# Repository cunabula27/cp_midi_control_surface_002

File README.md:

# midi_control_surface_002 Prototype
Midi Control Surface for Arduino Mega 2560 Rev3 running custom OpenDeck firmware available from www.shanteacontrols.com

This is the version that went into production and that I'm using myself. It contains some errors but they have no effect on functionality:

All the rotary potentiometers are wired in reverse, this is easily fixed by setting _Invert_ in the OpenDeck Configurator.

Also the rotary potentiometer footprints have incorrect design on the silk layer - I changed the type of potentiometer I was using after the boards were printed. Their physical footprint in the same but the sweep angle is greater so the panel graphics don't line up. This is purely cosmetic, but if you know me immensely annoying :)

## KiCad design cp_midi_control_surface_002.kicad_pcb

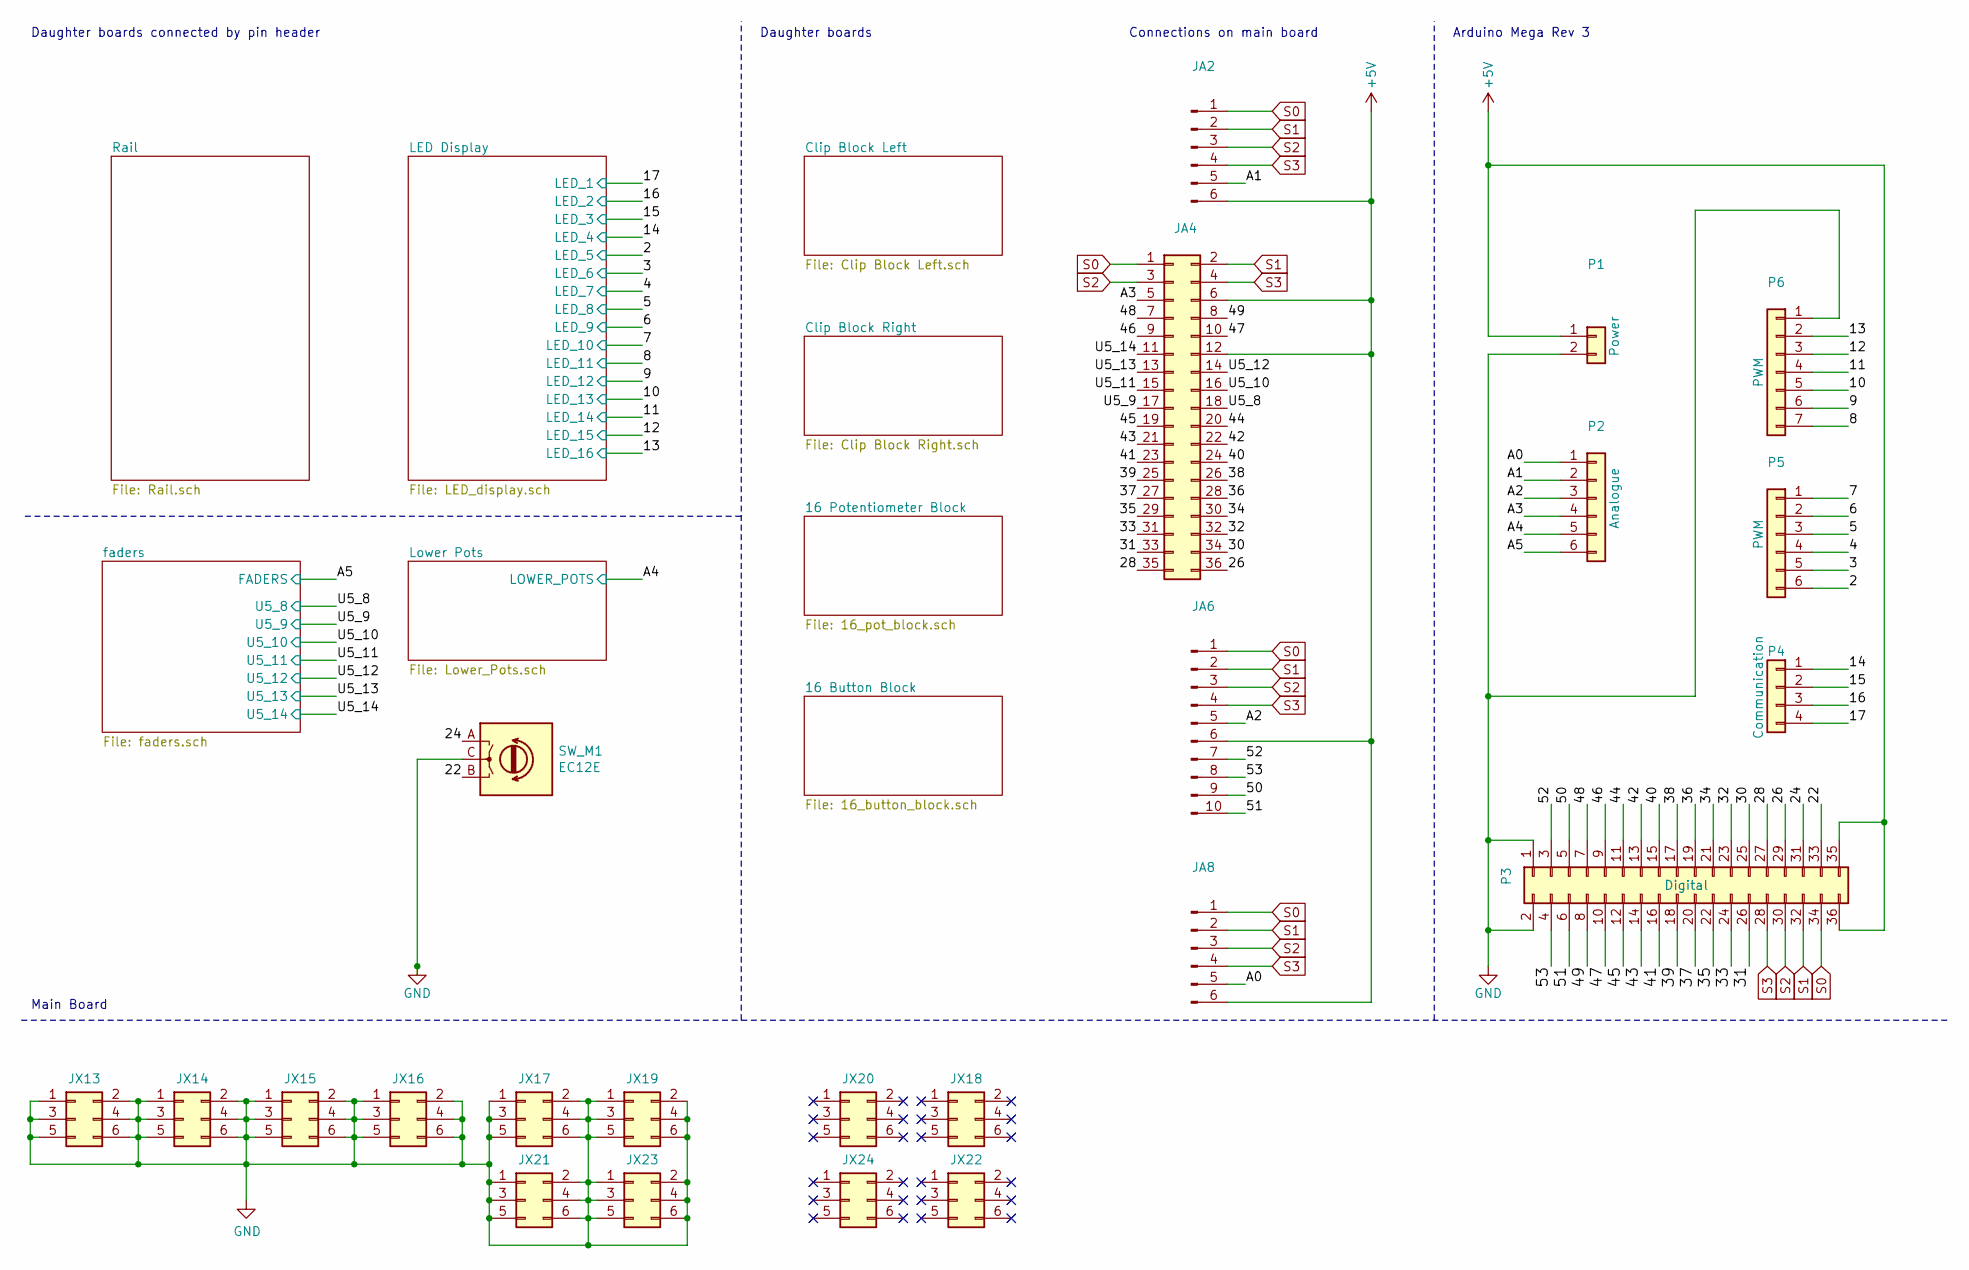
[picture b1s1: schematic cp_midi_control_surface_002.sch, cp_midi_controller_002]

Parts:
JA2, JA8: PinHeader_2x03_P2.54mm_Vertical
JA4: PinHeader_2x18_P2.54mm_Vertical
JA6: PinHeader_2x05_P2.54mm_Vertical
JX13, JX14, JX15, JX16, JX17, JX18, JX19, JX20, JX21, JX22, JX23, JX24: Conn_02x03_Odd_Even; PinHeader_2x03_P2.54mm_Vertical
P1: Power; PinHeader_1x02_P2.54mm_Vertical
P2: Analogue; PinHeader_1x06_P2.54mm_Vertical
P3: Digital; PinHeader_2x18_P2.54mm_Vertical
P4: Communication; PinHeader_1x04_P2.54mm_Vertical
P5: PWM; PinHeader_1x06_P2.54mm_Vertical
P6: PWM; PinHeader_1x07_P2.54mm_Vertical
SW_M1: EC12E; RotaryEncoder_Alps_EC12E_Vertical_H20mm_6_Preset_Silk_EDIT

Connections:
+5V: JA2.6, JA4.6, JA4.12, JA6.6, JA8.6, P1.1, P3.35, P3.36; also elsewhere on the board
/2: P5.6; also elsewhere on the board
/3: P5.5; also elsewhere on the board
/4: P5.4; also elsewhere on the board
/5: P5.3; also elsewhere on the board
/6: P5.2; also elsewhere on the board
/7: P5.1; also elsewhere on the board
/8: P6.7; also elsewhere on the board
/9: P6.6; also elsewhere on the board
/10: P6.5; also elsewhere on the board
/11: P6.4; also elsewhere on the board
/12: P6.3; also elsewhere on the board
/13: P6.2; also elsewhere on the board
/14: P4.1; also elsewhere on the board
/15: P4.2; also elsewhere on the board
/16: P4.3; also elsewhere on the board
/17: P4.4; also elsewhere on the board
/22: P3.33, SW_M1.B
/24: P3.31, SW_M1.A
/26: JA4.36, P3.29
/28: JA4.35, P3.27
/30: JA4.34, P3.25
/31: JA4.33, P3.26
/32: JA4.32, P3.23
/33: JA4.31, P3.24
/34: JA4.30, P3.21
/35: JA4.29, P3.22
/36: JA4.28, P3.19
/37: JA4.27, P3.20
/38: JA4.26, P3.17
/39: JA4.25, P3.18
/40: JA4.24, P3.15
/41: JA4.23, P3.16
/42: JA4.22, P3.13
/43: JA4.21, P3.14
/44: JA4.20, P3.11
/45: JA4.19, P3.12
/46: JA4.9, P3.9
/47: JA4.10, P3.10
/48: JA4.7, P3.7
/49: JA4.8, P3.8
/50: JA6.9, P3.5
/51: JA6.10, P3.6
/52: JA6.7, P3.3
/53: JA6.8, P3.4
/A0: JA8.5, P2.1
/A1: JA2.5, P2.2
/A2: JA6.5, P2.3
/A3: JA4.5, P2.4
/A4: P2.5; also elsewhere on the board
/A5: P2.6; also elsewhere on the board
/U5_8: JA4.18; also elsewhere on the board
/U5_9: JA4.17; also elsewhere on the board
/U5_10: JA4.16; also elsewhere on the board
/U5_11: JA4.15; also elsewhere on the board
/U5_12: JA4.14; also elsewhere on the board
/U5_13: JA4.13; also elsewhere on the board
/U5_14: JA4.11; also elsewhere on the board
GND: JX13.1, JX13.2, JX13.3, JX13.4, JX13.5, JX13.6, JX14.1, JX14.2, JX14.3, JX14.4, JX14.5, JX14.6, JX15.1, JX15.2, JX15.3, JX15.4, JX15.5, JX15.6, JX16.1, JX16.2, JX16.3, JX16.4, JX16.5, JX16.6, JX17.1, JX17.2, JX17.3, JX17.4, JX17.5, JX17.6, JX19.1, JX19.2, JX19.3, JX19.4, JX19.5, JX19.6, JX21.1, JX21.2, JX21.3, JX21.4, JX21.5, JX21.6, JX23.1, JX23.2, JX23.3, JX23.4, JX23.5, JX23.6, P1.2, P3.1, P3.2, P6.1, SW_M1.C; also elsewhere on the board
S0: JA2.1, JA4.1, JA6.1, JA8.1, P3.34; also elsewhere on the board
S1: JA2.2, JA4.2, JA6.2, JA8.2, P3.32; also elsewhere on the board
S2: JA2.3, JA4.3, JA6.3, JA8.3, P3.30; also elsewhere on the board
S3: JA2.4, JA4.4, JA6.4, JA8.4, P3.28; also elsewhere on the board

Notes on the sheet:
Arduino Mega Rev 3
Daughter boards
Daughter boards connected by pin header
Main Board
Connections on main board

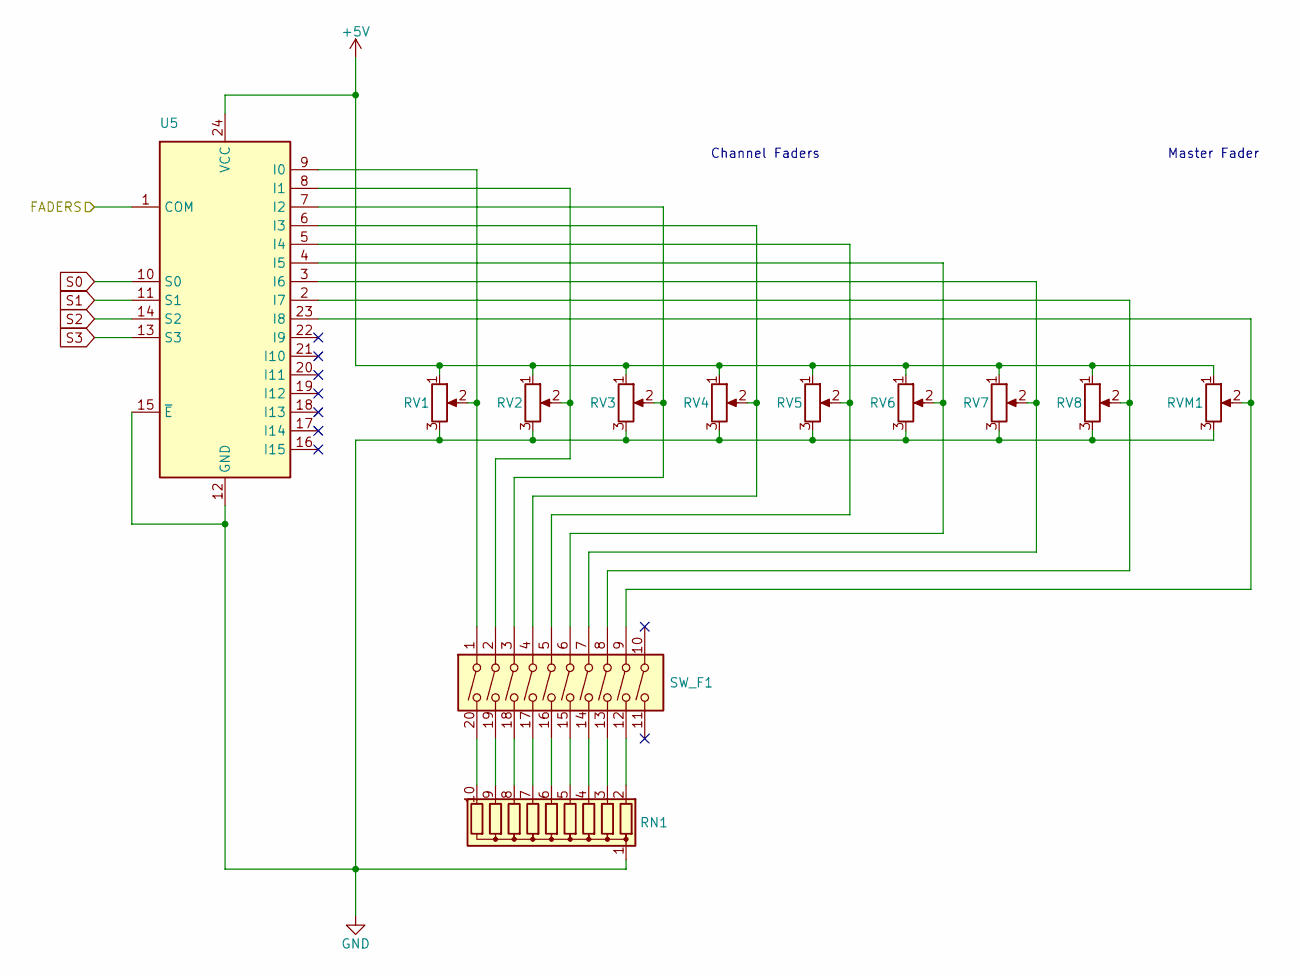
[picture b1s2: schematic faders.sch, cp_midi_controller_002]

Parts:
RN1: 2.2K (Bussed); R_Array_SIP10
RV1, RV2, RV3, RV4, RV5, RV6, RV7, RV8: PTA4543; Potentiometer_Bourns_PTA4543_Single_Slide_CP_EDIT
RVM1: PTA4543; Potentiometer_Bourns_PTA4543_Single_Slide_CP_EDIT
SW_F1: SW_DIP_x10; DIP-20_W7.62mm
U5: CD74HC4067M; SOIC-24W_7.5x15.4mm_P1.27mm

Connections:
+5V: RV1.1, RV2.1, RV3.1, RV4.1, RV5.1, RV6.1, RV7.1, RV8.1, RVM1.1, U5.24 (VCC); also elsewhere on the board
/A5: U5.1 (COM); also elsewhere on the board
/U5_8: U5.16 (I15); also elsewhere on the board
/U5_9: U5.17 (I14); also elsewhere on the board
/U5_10: U5.18 (I13); also elsewhere on the board
/U5_11: U5.19 (I12); also elsewhere on the board
/U5_12: U5.20 (I11); also elsewhere on the board
/U5_13: U5.21 (I10); also elsewhere on the board
/U5_14: U5.22 (I9); also elsewhere on the board
GND: RN1.1 (common), RV1.3, RV2.3, RV3.3, RV4.3, RV5.3, RV6.3, RV7.3, RV8.3, RVM1.3, U5.12 (GND), U5.15 (~E); also elsewhere on the board
unnamed: RN1.2 (R1), SW_F1.12
unnamed: RN1.3 (R2), SW_F1.13
unnamed: RN1.4 (R3), SW_F1.14
unnamed: RN1.5 (R4), SW_F1.15
unnamed: RN1.6 (R5), SW_F1.16
unnamed: RN1.7 (R6), SW_F1.17
unnamed: RN1.8 (R7), SW_F1.18
unnamed: RN1.9 (R8), SW_F1.19
unnamed: RN1.10 (R9), SW_F1.20
unnamed: RV1.2, SW_F1.1, U5.9 (I0)
unnamed: RV2.2, SW_F1.2, U5.8 (I1)
unnamed: RV3.2, SW_F1.3, U5.7 (I2)
unnamed: RV4.2, SW_F1.4, U5.6 (I3)
unnamed: RV5.2, SW_F1.5, U5.5 (I4)
unnamed: RV6.2, SW_F1.6, U5.4 (I5)
unnamed: RV7.2, SW_F1.7, U5.3 (I6)
unnamed: RV8.2, SW_F1.8, U5.2 (I7)
unnamed: RVM1.2, SW_F1.9, U5.23 (I8)
S0: U5.10 (S0); also elsewhere on the board
S1: U5.11 (S1); also elsewhere on the board
S2: U5.14 (S2); also elsewhere on the board
S3: U5.13 (S3); also elsewhere on the board

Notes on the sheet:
Channel Faders
Master Fader

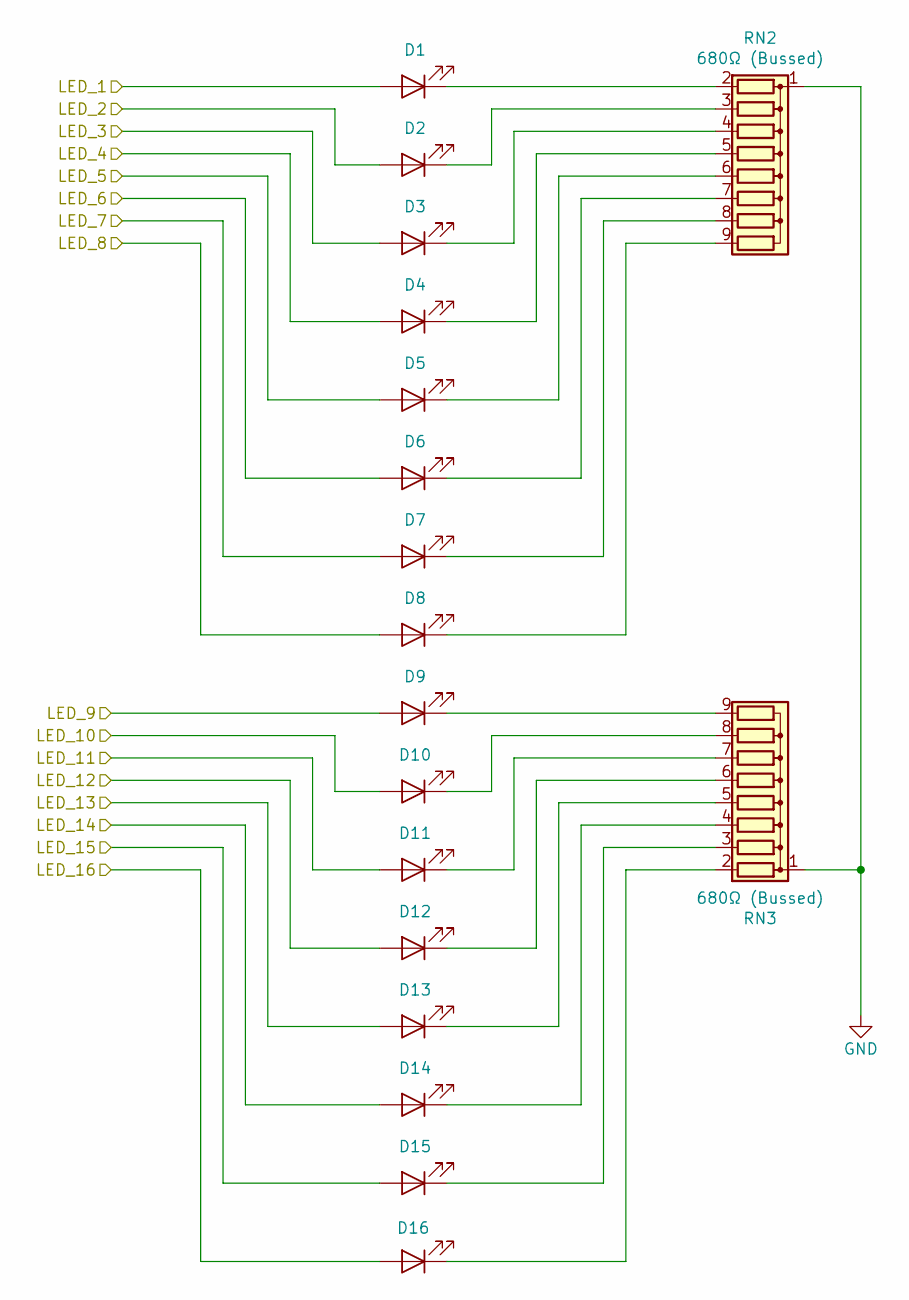
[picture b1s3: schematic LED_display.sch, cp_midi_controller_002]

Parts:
D1, D2, D3, D4, D5, D6, D7, D8, D9, D10, D11, D12, D13, D14, D15, D16: LED; LED_D3.0mm_EDIT
RN2, RN3: 680Ω (Bussed); R_Array_SIP9

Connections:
/2: D5.2 (A); also elsewhere on the board
/3: D6.2 (A); also elsewhere on the board
/4: D7.2 (A); also elsewhere on the board
/5: D8.2 (A); also elsewhere on the board
/6: D9.2 (A); also elsewhere on the board
/7: D10.2 (A); also elsewhere on the board
/8: D11.2 (A); also elsewhere on the board
/9: D12.2 (A); also elsewhere on the board
/10: D13.2 (A); also elsewhere on the board
/11: D14.2 (A); also elsewhere on the board
/12: D15.2 (A); also elsewhere on the board
/13: D16.2 (A); also elsewhere on the board
/14: D4.2 (A); also elsewhere on the board
/15: D3.2 (A); also elsewhere on the board
/16: D2.2 (A); also elsewhere on the board
/17: D1.2 (A); also elsewhere on the board
GND: RN2.1 (common), RN3.1 (common); also elsewhere on the board
unnamed: D1.1 (K), RN2.2 (R1)
unnamed: D2.1 (K), RN2.3 (R2)
unnamed: D3.1 (K), RN2.4 (R3)
unnamed: D4.1 (K), RN2.5 (R4)
unnamed: D5.1 (K), RN2.6 (R5)
unnamed: D6.1 (K), RN2.7 (R6)
unnamed: D7.1 (K), RN2.8 (R7)
unnamed: D8.1 (K), RN2.9 (R8)
unnamed: D9.1 (K), RN3.9 (R8)
unnamed: D10.1 (K), RN3.8 (R7)
unnamed: D11.1 (K), RN3.7 (R6)
unnamed: D12.1 (K), RN3.6 (R5)
unnamed: D13.1 (K), RN3.5 (R4)
unnamed: D14.1 (K), RN3.4 (R3)
unnamed: D15.1 (K), RN3.3 (R2)
unnamed: D16.1 (K), RN3.2 (R1)

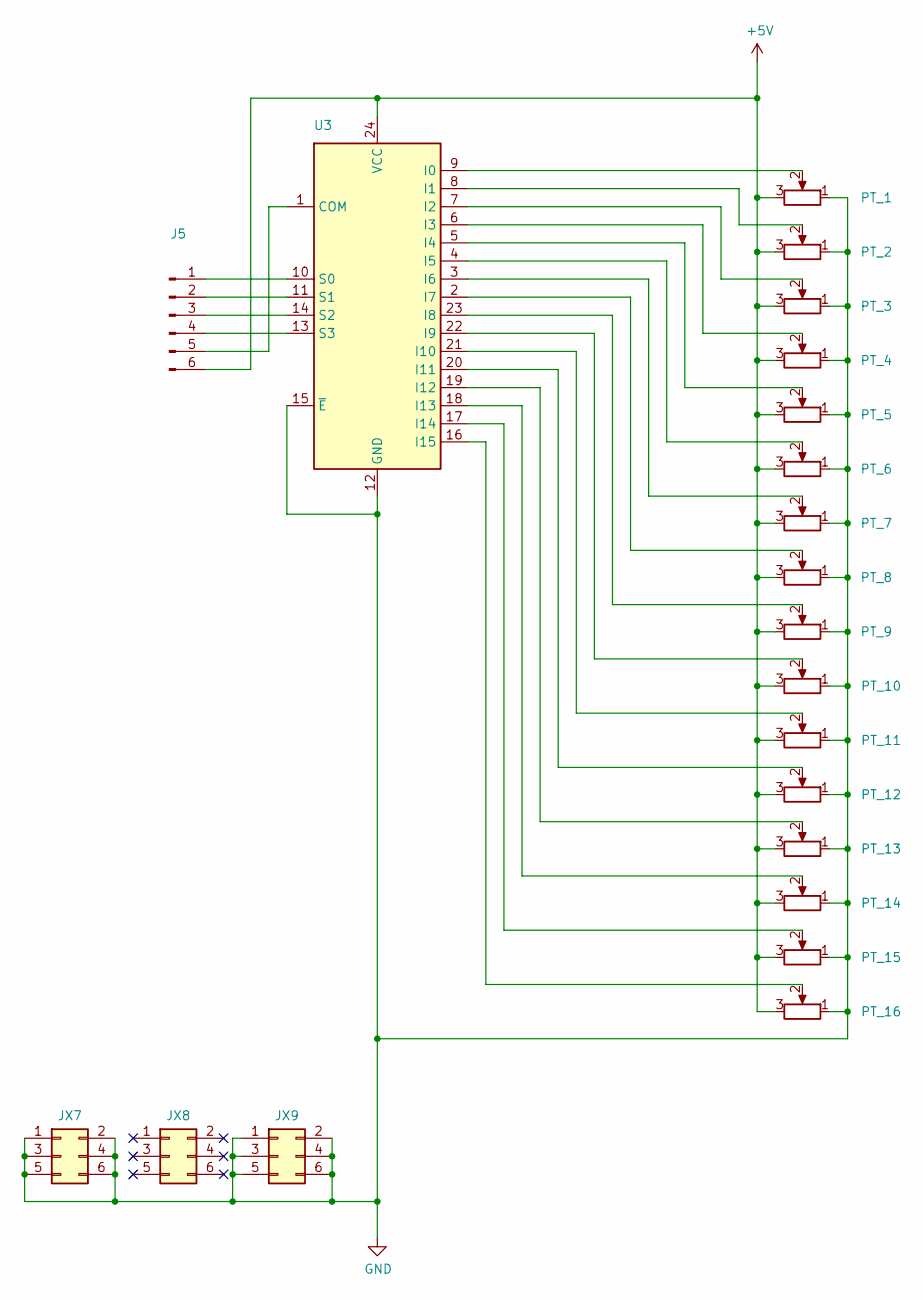
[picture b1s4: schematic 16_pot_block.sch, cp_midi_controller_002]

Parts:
J5: PinHeader_2x03_P2.54mm_Vertical
JX7, JX8, JX9: Conn_02x03_Odd_Even; PinHeader_2x03_P2.54mm_Vertical
PT_1, PT_2, PT_3, PT_4, PT_5, PT_6, PT_7, PT_8, PT_9, PT_10, PT_11, PT_12, PT_13, PT_14, PT_15, PT_16: 10k; Potentiometer_Alps_RK09D1130X
U3: CD74HC4067M; SOIC-24W_7.5x15.4mm_P1.27mm

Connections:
+5V: J5.6, PT_1.3, PT_2.3, PT_3.3, PT_4.3, PT_5.3, PT_6.3, PT_7.3, PT_8.3, PT_9.3, PT_10.3, PT_11.3, PT_12.3, PT_13.3, PT_14.3, PT_15.3, PT_16.3, U3.24 (VCC); also elsewhere on the board
GND: JX7.1, JX7.2, JX7.3, JX7.4, JX7.5, JX7.6, JX9.1, JX9.2, JX9.3, JX9.4, JX9.5, JX9.6, PT_1.1, PT_2.1, PT_3.1, PT_4.1, PT_5.1, PT_6.1, PT_7.1, PT_8.1, PT_9.1, PT_10.1, PT_11.1, PT_12.1, PT_13.1, PT_14.1, PT_15.1, PT_16.1, U3.12 (GND), U3.15 (~E); also elsewhere on the board
unnamed: J5.1, U3.10 (S0)
unnamed: J5.2, U3.11 (S1)
unnamed: J5.3, U3.14 (S2)
unnamed: J5.4, U3.13 (S3)
unnamed: J5.5, U3.1 (COM)
unnamed: PT_1.2, U3.9 (I0)
unnamed: PT_2.2, U3.8 (I1)
unnamed: PT_3.2, U3.7 (I2)
unnamed: PT_4.2, U3.6 (I3)
unnamed: PT_5.2, U3.5 (I4)
unnamed: PT_6.2, U3.4 (I5)
unnamed: PT_7.2, U3.3 (I6)
unnamed: PT_8.2, U3.2 (I7)
unnamed: PT_9.2, U3.23 (I8)
unnamed: PT_10.2, U3.22 (I9)
unnamed: PT_11.2, U3.21 (I10)
unnamed: PT_12.2, U3.20 (I11)
unnamed: PT_13.2, U3.19 (I12)
unnamed: PT_14.2, U3.18 (I13)
unnamed: PT_15.2, U3.17 (I14)
unnamed: PT_16.2, U3.16 (I15)

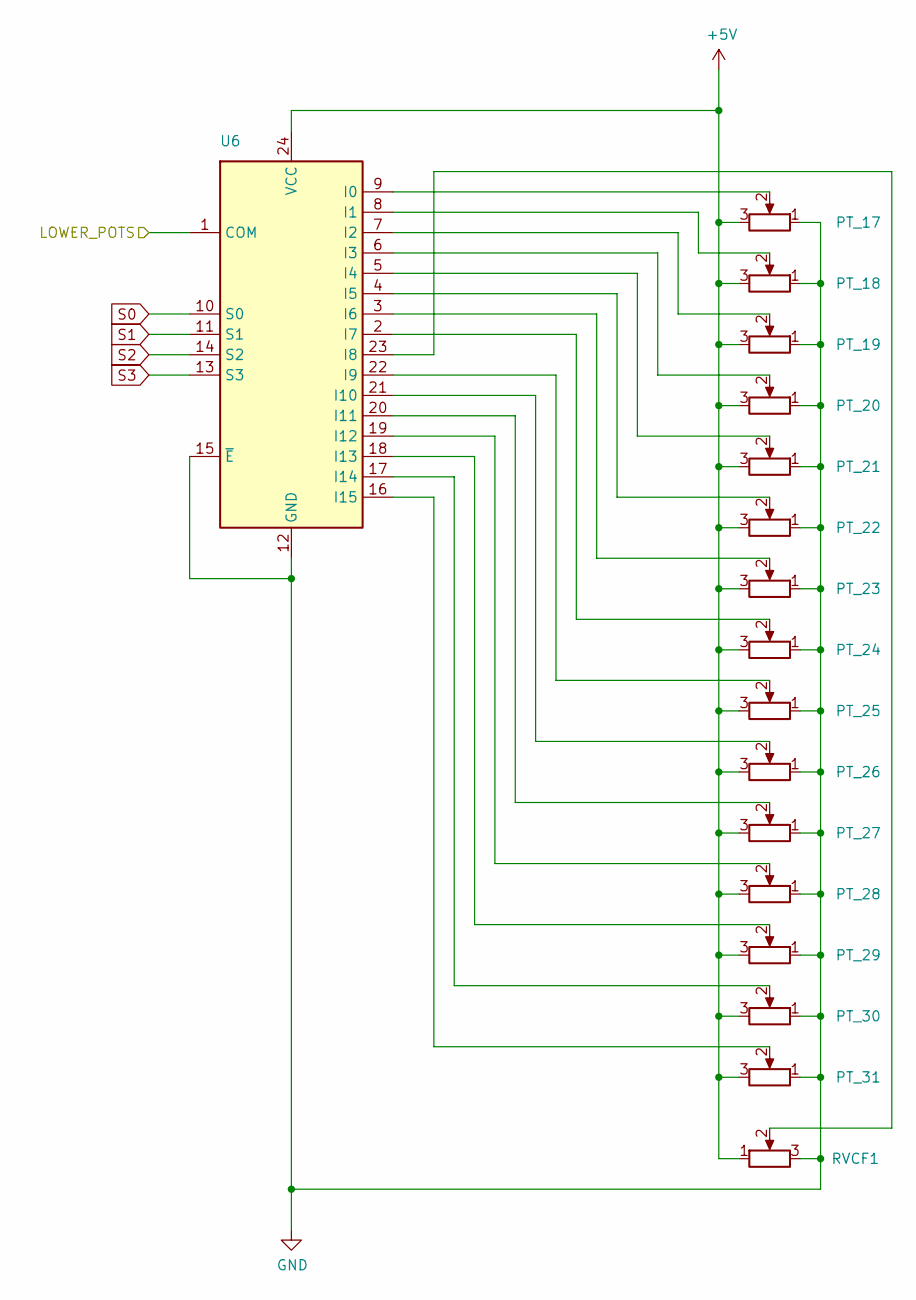
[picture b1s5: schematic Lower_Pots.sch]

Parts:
PT_17, PT_18, PT_19, PT_20, PT_21, PT_22, PT_23, PT_24, PT_25, PT_26, PT_27, PT_28, PT_29, PT_30, PT_31: 10k; Potentiometer_Alps_RK09D1130X
RVCF1: PTA4543; Potentiometer_Bourns_PTA4543_Single_Slide_CP_EDIT
U6: CD74HC4067M; SOIC-24W_7.5x15.4mm_P1.27mm

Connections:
+5V: PT_17.3, PT_18.3, PT_19.3, PT_20.3, PT_21.3, PT_22.3, PT_23.3, PT_24.3, PT_25.3, PT_26.3, PT_27.3, PT_28.3, PT_29.3, PT_30.3, PT_31.3, RVCF1.1, U6.24 (VCC); also elsewhere on the board
/A4: U6.1 (COM); also elsewhere on the board
GND: PT_17.1, PT_18.1, PT_19.1, PT_20.1, PT_21.1, PT_22.1, PT_23.1, PT_24.1, PT_25.1, PT_26.1, PT_27.1, PT_28.1, PT_29.1, PT_30.1, PT_31.1, RVCF1.3, U6.12 (GND), U6.15 (~E); also elsewhere on the board
unnamed: PT_17.2, U6.9 (I0)
unnamed: PT_18.2, U6.8 (I1)
unnamed: PT_19.2, U6.7 (I2)
unnamed: PT_20.2, U6.6 (I3)
unnamed: PT_21.2, U6.5 (I4)
unnamed: PT_22.2, U6.4 (I5)
unnamed: PT_23.2, U6.3 (I6)
unnamed: PT_24.2, U6.2 (I7)
unnamed: PT_25.2, U6.22 (I9)
unnamed: PT_26.2, U6.21 (I10)
unnamed: PT_27.2, U6.20 (I11)
unnamed: PT_28.2, U6.19 (I12)
unnamed: PT_29.2, U6.18 (I13)
unnamed: PT_30.2, U6.17 (I14)
unnamed: PT_31.2, U6.16 (I15)
unnamed: RVCF1.2, U6.23 (I8)
S0: U6.10 (S0); also elsewhere on the board
S1: U6.11 (S1); also elsewhere on the board
S2: U6.14 (S2); also elsewhere on the board
S3: U6.13 (S3); also elsewhere on the board

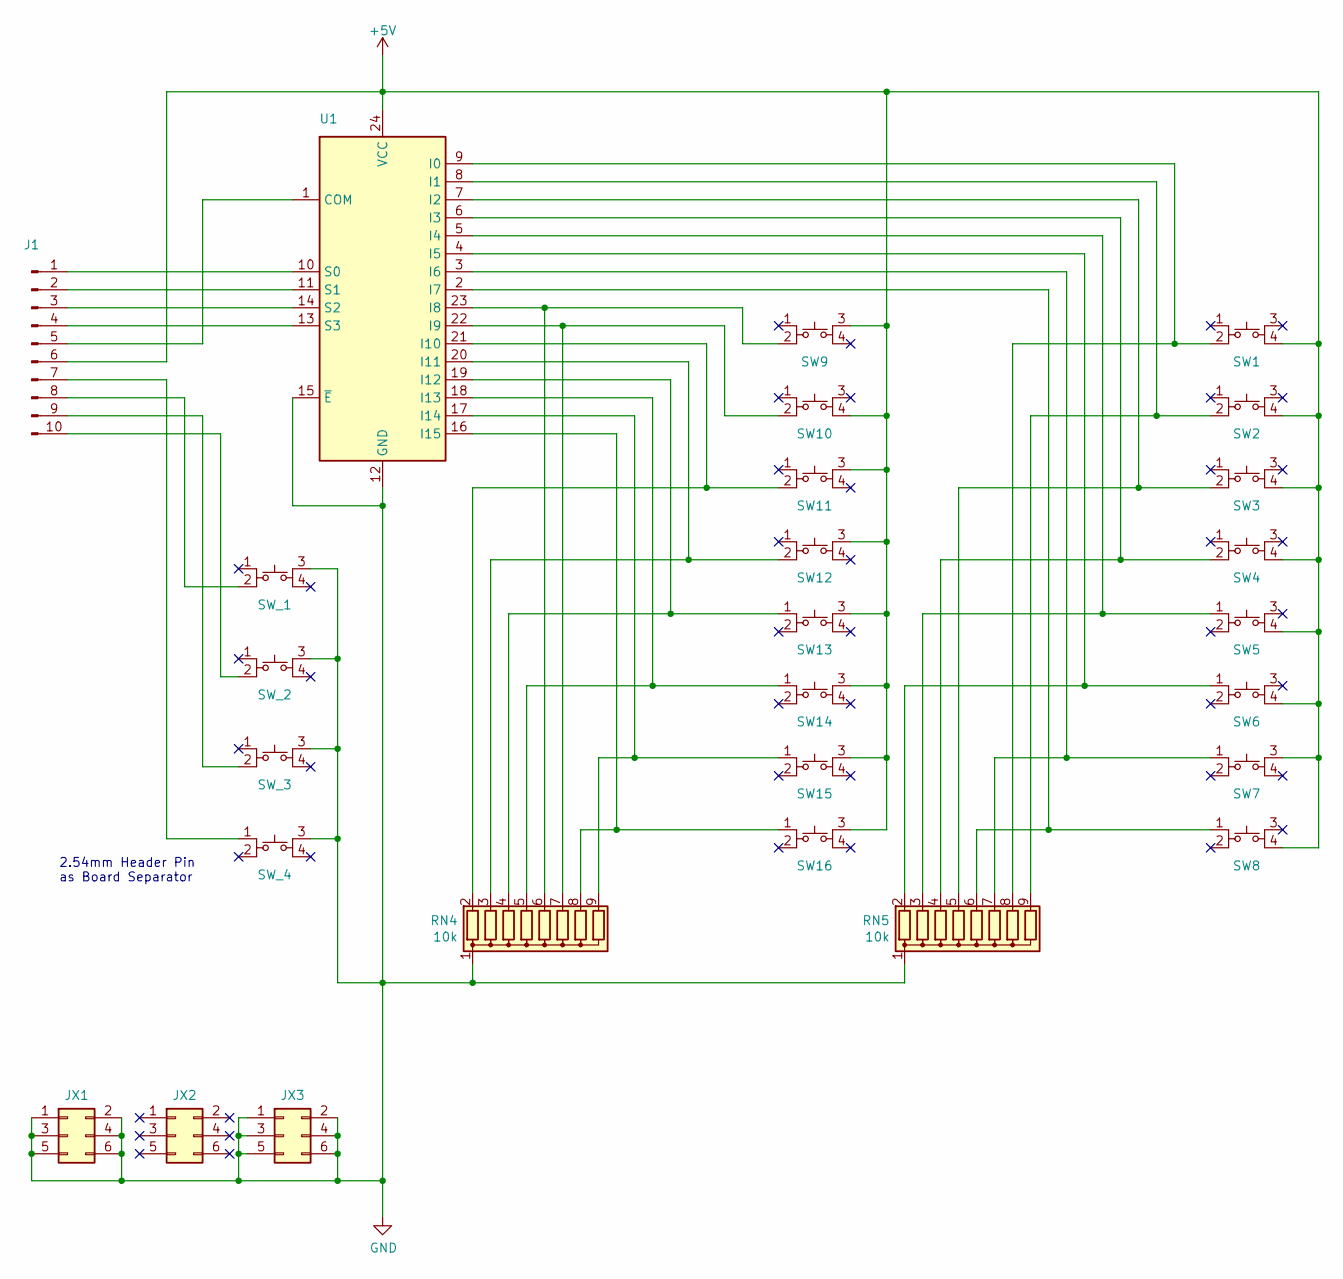
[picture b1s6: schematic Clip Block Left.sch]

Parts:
J1: Conn_02x05_Odd_Even; PinHeader_2x05_P2.54mm_Vertical
JX1, JX2, JX3: Conn_02x03_Odd_Even; PinHeader_2x03_P2.54mm_Vertical
RN4, RN5: 10k; R_Array_SIP9
SW1, SW2, SW3, SW4, SW5, SW6, SW7, SW8, SW9, SW10, SW11, SW12, SW13, SW14, SW15, SW16: B3F-5050; Omron_B3F-5050
SW_1, SW_2, SW_3, SW_4: B3F-5050; Omron_B3F-5050
U1: CD74HC4067M; SOIC-24W_7.5x15.4mm_P1.27mm

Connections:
+5V: J1.6, SW1.4, SW2.4, SW3.4, SW4.4, SW5.4, SW6.4, SW7.3, SW8.4, SW9.3, SW10.4, SW11.3, SW12.3, SW13.3, SW14.3, SW15.3, SW16.3, U1.24 (VCC); also elsewhere on the board
GND: JX1.1, JX1.2, JX1.3, JX1.4, JX1.5, JX1.6, JX3.1, JX3.2, JX3.3, JX3.4, JX3.5, JX3.6, RN4.1 (common), RN5.1 (common), SW_1.3, SW_2.3, SW_3.3, SW_4.3, U1.12 (GND), U1.15 (~E); also elsewhere on the board
unnamed: J1.1, U1.10 (S0)
unnamed: J1.2, U1.11 (S1)
unnamed: J1.3, U1.14 (S2)
unnamed: J1.4, U1.13 (S3)
unnamed: J1.5, U1.1 (COM)
unnamed: J1.7, SW_4.1 (A)
unnamed: J1.8, SW_1.2
unnamed: J1.9, SW_3.2
unnamed: J1.10, SW_2.2
unnamed: RN4.2 (R1), SW11.2, U1.21 (I10)
unnamed: RN4.3 (R2), SW12.2, U1.20 (I11)
unnamed: RN4.4 (R3), SW13.1 (A), U1.19 (I12)
unnamed: RN4.5 (R4), SW14.1 (A), U1.18 (I13)
unnamed: RN4.6 (R5), SW9.2, U1.23 (I8)
unnamed: RN4.7 (R6), SW10.2, U1.22 (I9)
unnamed: RN4.8 (R7), SW16.1 (A), U1.16 (I15)
unnamed: RN4.9 (R8), SW15.1 (A), U1.17 (I14)
unnamed: RN5.2 (R1), SW6.1 (A), U1.4 (I5)
unnamed: RN5.3 (R2), SW5.1 (A), U1.5 (I4)
unnamed: RN5.4 (R3), SW4.2, U1.6 (I3)
unnamed: RN5.5 (R4), SW3.2, U1.7 (I2)
unnamed: RN5.6 (R5), SW8.1 (A), U1.2 (I7)
unnamed: RN5.7 (R6), SW7.1 (A), U1.3 (I6)
unnamed: RN5.8 (R7), SW1.2, U1.9 (I0)
unnamed: RN5.9 (R8), SW2.2, U1.8 (I1)

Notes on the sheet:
2.54mm Header Pin as Board Separator

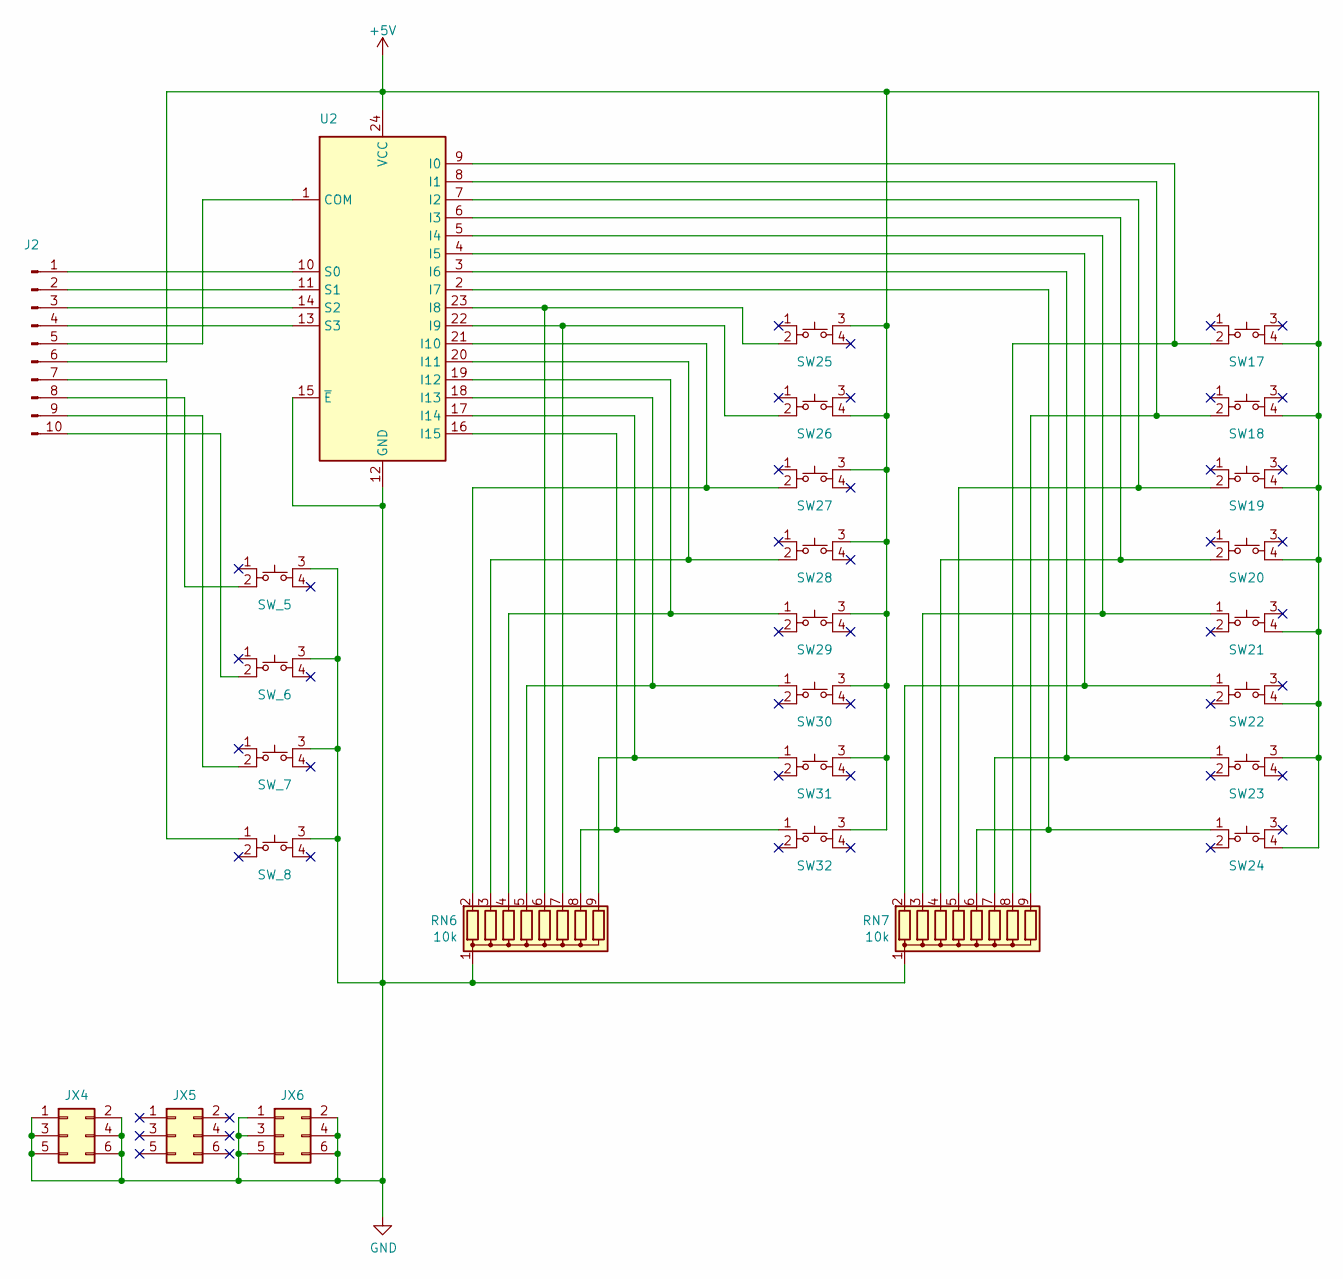
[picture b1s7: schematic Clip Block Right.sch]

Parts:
J2: Conn_02x05_Odd_Even; PinHeader_2x05_P2.54mm_Vertical
JX4, JX5, JX6: Conn_02x03_Odd_Even; PinHeader_2x03_P2.54mm_Vertical
RN6, RN7: 10k; R_Array_SIP9
SW17, SW18, SW19, SW20, SW21, SW22, SW23, SW24, SW25, SW26, SW27, SW28, SW29, SW30, SW31, SW32: B3F-5050; Omron_B3F-5050
SW_5, SW_6, SW_7, SW_8: B3F-5050; Omron_B3F-5050
U2: CD74HC4067M; SOIC-24W_7.5x15.4mm_P1.27mm

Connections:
+5V: J2.6, SW17.4, SW18.4, SW19.4, SW20.4, SW21.4, SW22.4, SW23.3, SW24.4, SW25.3, SW26.4, SW27.3, SW28.3, SW29.3, SW30.3, SW31.3, SW32.3, U2.24 (VCC); also elsewhere on the board
GND: JX4.1, JX4.2, JX4.3, JX4.4, JX4.5, JX4.6, JX6.1, JX6.2, JX6.3, JX6.4, JX6.5, JX6.6, RN6.1 (common), RN7.1 (common), SW_5.3, SW_6.3, SW_7.3, SW_8.3, U2.12 (GND), U2.15 (~E); also elsewhere on the board
unnamed: J2.1, U2.10 (S0)
unnamed: J2.2, U2.11 (S1)
unnamed: J2.3, U2.14 (S2)
unnamed: J2.4, U2.13 (S3)
unnamed: J2.5, U2.1 (COM)
unnamed: J2.7, SW_8.1 (A)
unnamed: J2.8, SW_5.2
unnamed: J2.9, SW_7.2
unnamed: J2.10, SW_6.2
unnamed: RN6.2 (R1), SW27.2, U2.21 (I10)
unnamed: RN6.3 (R2), SW28.2, U2.20 (I11)
unnamed: RN6.4 (R3), SW29.1 (A), U2.19 (I12)
unnamed: RN6.5 (R4), SW30.1 (A), U2.18 (I13)
unnamed: RN6.6 (R5), SW25.2, U2.23 (I8)
unnamed: RN6.7 (R6), SW26.2, U2.22 (I9)
unnamed: RN6.8 (R7), SW32.1 (A), U2.16 (I15)
unnamed: RN6.9 (R8), SW31.1 (A), U2.17 (I14)
unnamed: RN7.2 (R1), SW22.1 (A), U2.4 (I5)
unnamed: RN7.3 (R2), SW21.1 (A), U2.5 (I4)
unnamed: RN7.4 (R3), SW20.2, U2.6 (I3)
unnamed: RN7.5 (R4), SW19.2, U2.7 (I2)
unnamed: RN7.6 (R5), SW24.1 (A), U2.2 (I7)
unnamed: RN7.7 (R6), SW23.1 (A), U2.3 (I6)
unnamed: RN7.8 (R7), SW17.2, U2.9 (I0)
unnamed: RN7.9 (R8), SW18.2, U2.8 (I1)

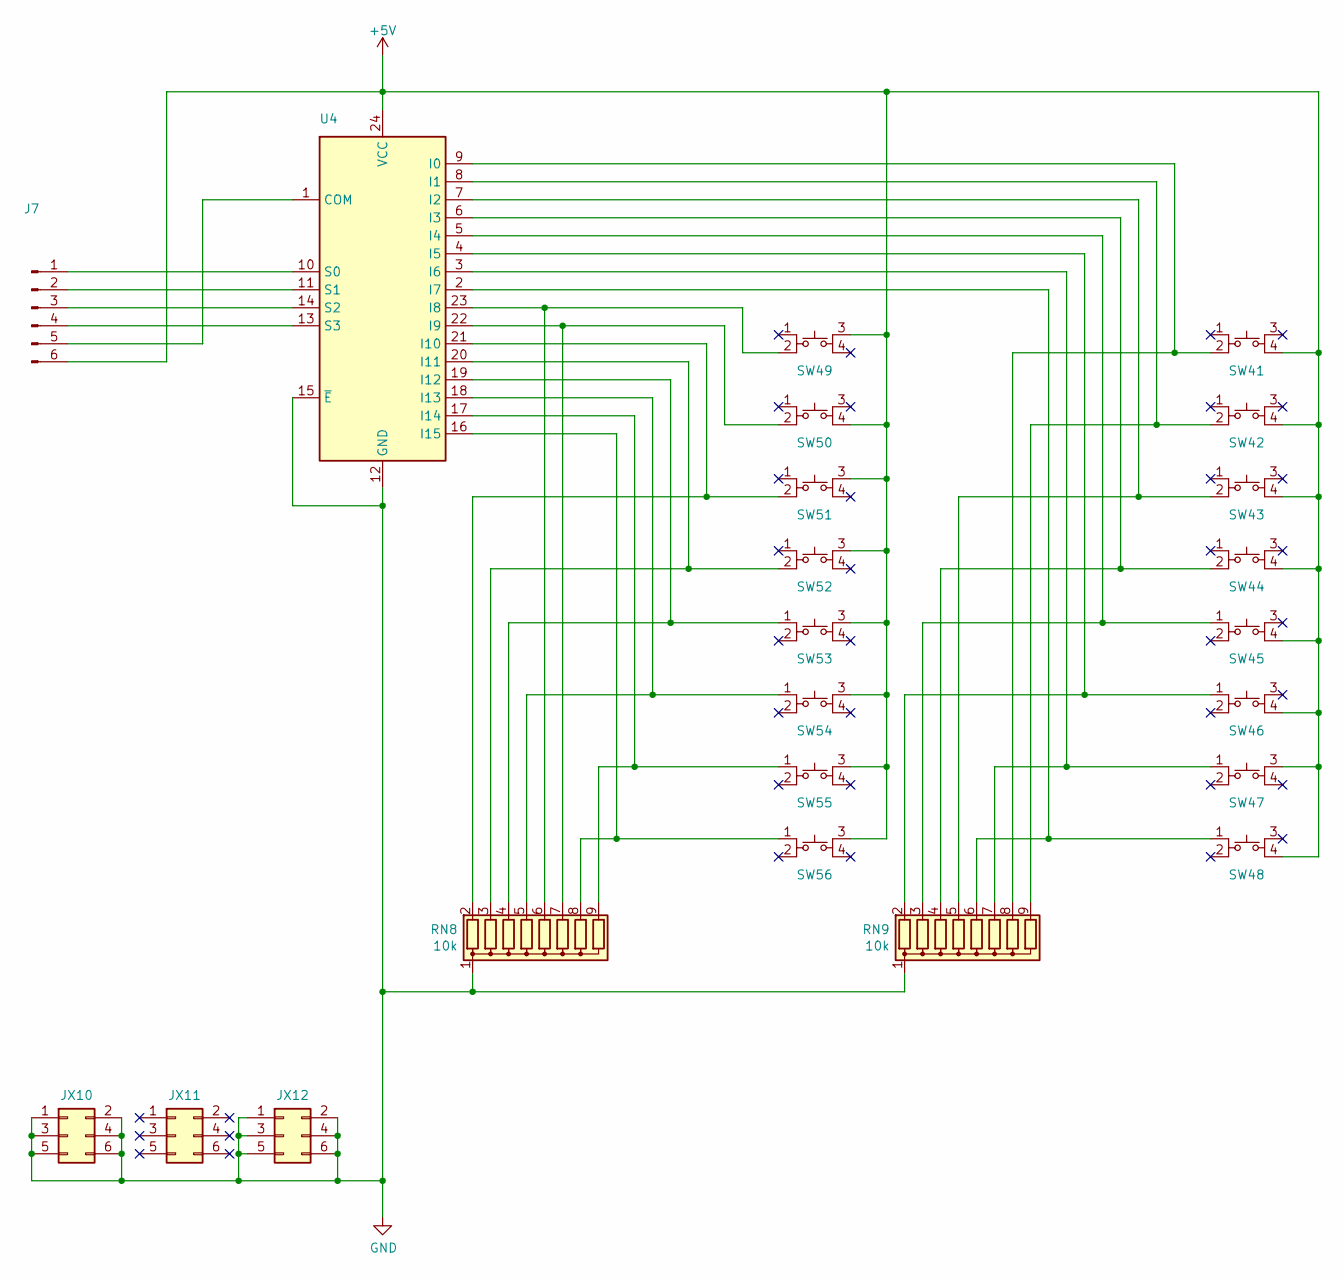
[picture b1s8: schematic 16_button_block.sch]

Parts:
J7: Conn_02x05_Odd_Even; PinHeader_2x03_P2.54mm_Vertical
JX10, JX11, JX12: Conn_02x03_Odd_Even; PinHeader_2x03_P2.54mm_Vertical
RN8, RN9: 10k; R_Array_SIP9
SW41, SW42, SW43, SW44, SW45, SW46, SW47, SW48, SW49, SW50, SW51, SW52, SW53, SW54, SW55, SW56: B3F-5050; Omron_B3F-5050
U4: CD74HC4067M; SOIC-24W_7.5x15.4mm_P1.27mm

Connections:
+5V: J7.6, SW41.4, SW42.4, SW43.4, SW44.4, SW45.4, SW46.4, SW47.3, SW48.4, SW49.3, SW50.4, SW51.3, SW52.3, SW53.3, SW54.3, SW55.3, SW56.3, U4.24 (VCC); also elsewhere on the board
GND: JX10.1, JX10.2, JX10.3, JX10.4, JX10.5, JX10.6, JX12.1, JX12.2, JX12.3, JX12.4, JX12.5, JX12.6, RN8.1 (common), RN9.1 (common), U4.12 (GND), U4.15 (~E); also elsewhere on the board
unnamed: J7.1, U4.10 (S0)
unnamed: J7.2, U4.11 (S1)
unnamed: J7.3, U4.14 (S2)
unnamed: J7.4, U4.13 (S3)
unnamed: J7.5, U4.1 (COM)
unnamed: RN8.2 (R1), SW51.2, U4.21 (I10)
unnamed: RN8.3 (R2), SW52.2, U4.20 (I11)
unnamed: RN8.4 (R3), SW53.1 (A), U4.19 (I12)
unnamed: RN8.5 (R4), SW54.1 (A), U4.18 (I13)
unnamed: RN8.6 (R5), SW49.2, U4.23 (I8)
unnamed: RN8.7 (R6), SW50.2, U4.22 (I9)
unnamed: RN8.8 (R7), SW56.1 (A), U4.16 (I15)
unnamed: RN8.9 (R8), SW55.1 (A), U4.17 (I14)
unnamed: RN9.2 (R1), SW46.1 (A), U4.4 (I5)
unnamed: RN9.3 (R2), SW45.1 (A), U4.5 (I4)
unnamed: RN9.4 (R3), SW44.2, U4.6 (I3)
unnamed: RN9.5 (R4), SW43.2, U4.7 (I2)
unnamed: RN9.6 (R5), SW48.1 (A), U4.2 (I7)
unnamed: RN9.7 (R6), SW47.1 (A), U4.3 (I6)
unnamed: RN9.8 (R7), SW41.2, U4.9 (I0)
unnamed: RN9.9 (R8), SW42.2, U4.8 (I1)

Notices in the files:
16_pot_block.sch:
Licence: CC BY SA
